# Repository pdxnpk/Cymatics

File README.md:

# Cymatics

Integrated PCBs for AudioLux and Vibrosonics

# Development

Install KiCad (version 8.0 or higher): https://www.kicad.org/download/

Open KiCad project file (Cymatics/Cymatics.kicad_pro)

# Build a PCB

## Order PCB

Go to JLCPCB (https://jlcpcb.com/) or PCBWay (https://www.pcbway.com/) to order a PCB

Start an order for a 2-layer PCB (Standard)

Add zip file of Gerber and Drill files (Fabrication/Cymatics_Gerber_Drill_03-21-25.zip)

Default specifications and options are OK

## Parts and Assembly

You may choose to have the PCB manufacturer assemble the boards for you, or you may order the parts separately and assemble the board on your own.

### Order PCB assembly

Provide the BOM and CPL (component placement list, or Centroid) for the manufacturer when requesting PCB assembly.

- Fabrication/Fabrication-BOM.xlsx: BOM adhering to PCBWay format (may need to revise for other manufacturers)

- Fabrication/Fabrication-CPL.csv: CPL or Centroid

### Order components separately

Open shopping list (Shopping-List.csv) to find links to order parts

Go to DigiKey (https://www.digikey.com/) and order listed part quanities

# Program the Microcontroller

To program the ESP32 with AudioLux and/or VibroSonics software, refer to their respective GitHub repositories.

- AudioLux software: https://github.com/OPEnSLab-OSU/Nanolux

- VibroSonics software: https://github.com/udellc/Vibrosonics

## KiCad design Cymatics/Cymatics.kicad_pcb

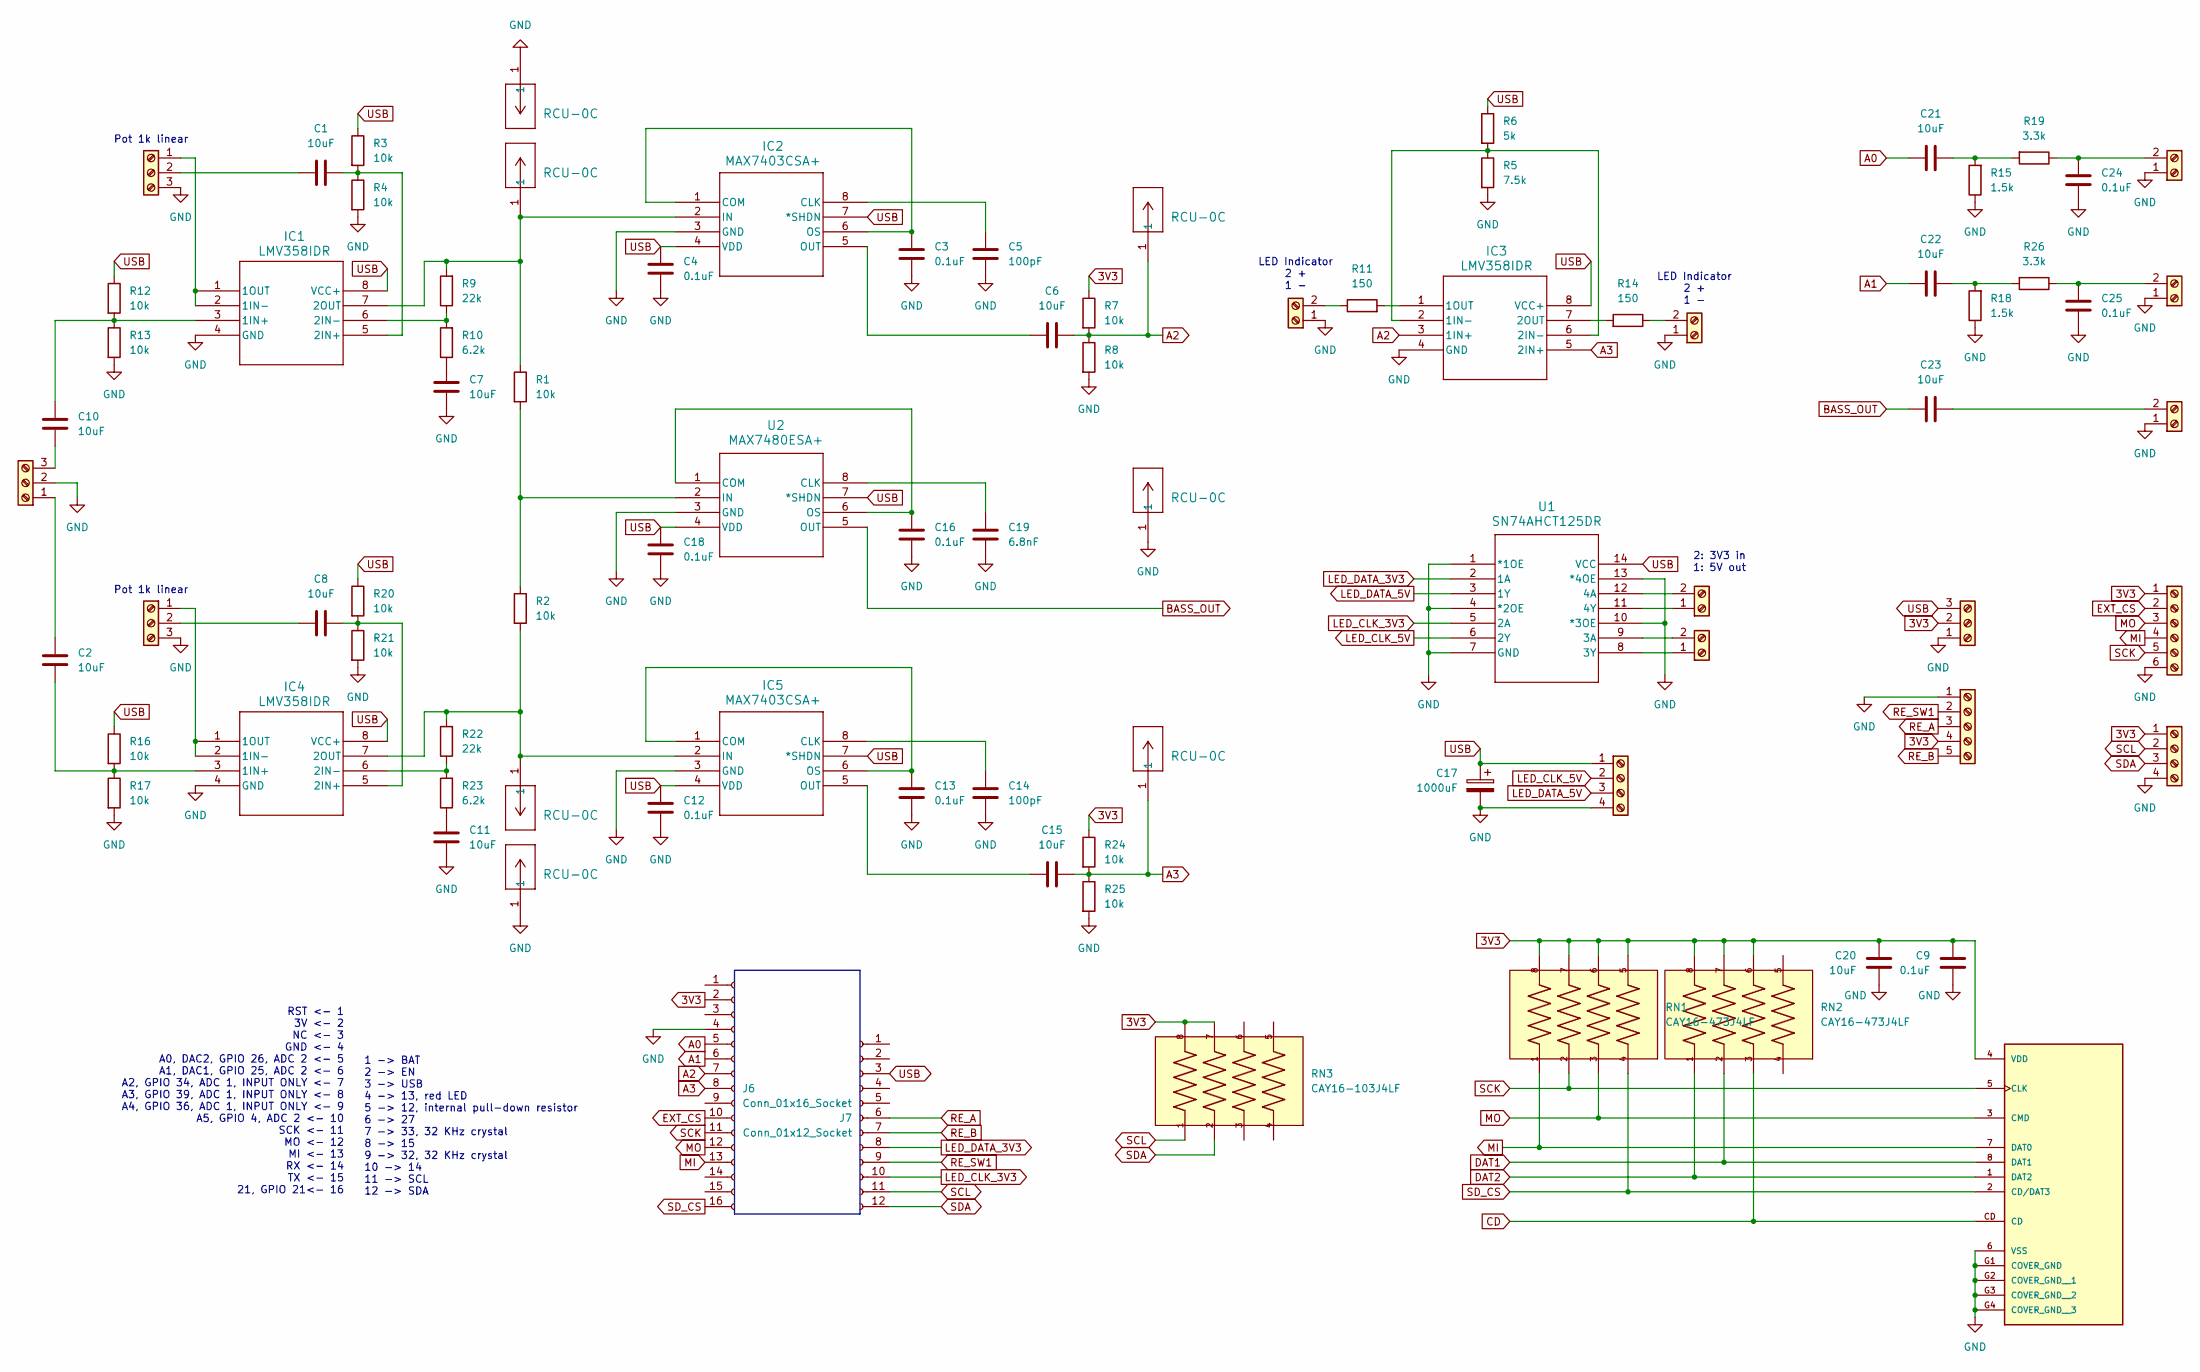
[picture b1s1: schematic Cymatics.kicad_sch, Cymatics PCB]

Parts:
C1, C2, C6, C7, C8, C10, C11, C15, C20, C21, C22, C23: 10uF; C_0805_2012Metric
C3, C4, C9, C12, C13, C16, C18, C24, C25: 0.1uF; C_0805_2012Metric
C5, C14: 100pF; C_0805_2012Metric
C17: 1000uF; CP_Radial_D8.0mm_P5.00mm
C19: 6.8nF; C_0805_2012Metric
IC1, IC3, IC4: LMV358IDR; D8
IC2, IC5: MAX7403CSA+; 21-0041B_8_MXM
J1, J3, J4, J16: Screw_Terminal_01x03; TerminalBlock_TE_282834-3_1x03_P2.54mm_Horizontal
J2, J5, J9, J12, J13, J15, J17: Screw_Terminal_01x02; TerminalBlock_TE_282834-2_1x02_P2.54mm_Horizontal
J6: Conn_01x16_Socket; PinSocket_1x16_P2.54mm_Vertical
J7: Conn_01x12_Socket; PinSocket_1x12_P2.54mm_Vertical
J8, J10: Screw_Terminal_01x04; TerminalBlock_TE_282834-4_1x04_P2.54mm_Horizontal
J11: Screw_Terminal_01x05; TerminalBlock_TE_282834-5_1x05_P2.54mm_Horizontal
J14, J19, J20, J21, J22, J23, J24: RCU-0C; CONN1_RCU-0C_TEC
J18: Screw_Terminal_01x06; TerminalBlock_TE_282834-6_1x06_P2.54mm_Horizontal
R1, R2, R3, R4, R7, R8, R12, R13, R16, R17, R20, R21, R24, R25: 10k; R_1206_3216Metric
R5: 7.5k; R_1206_3216Metric
R6: 5k; R_1206_3216Metric
R9, R22: 22k; R_1206_3216Metric
R10, R23: 6.2k; R_1206_3216Metric
R11, R14: 150; R_1206_3216Metric
R15, R18: 1.5k; R_1206_3216Metric
R19, R26: 3.3k; R_1206_3216Metric
RN1, RN2: CAY16-473J4LF; RESCAF80P320X160X60-8N
RN3: CAY16-103J4LF; RESCAF80P320X160X60-8N
SD1: MSD-4-A; CUI_MSD-4-A; PARTREV 1.0
U1: SN74AHCT125DR; D14
U2: MAX7480ESA+; 21-0041B_8_MXM

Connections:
3V3: C9.2, C20.1, J1.2, J6.2, J8.1, J11.4, J18.1, R7.1, R24.1, RN1.5, RN1.6, RN1.7, RN1.8, RN2.6, RN2.7, RN2.8, RN3.7, RN3.8, SD1.4 (VDD)
A0: C21.2, J6.5
A1: C22.2, J6.6
A2: C6.1, IC3.3 (1IN+), J6.7, J22.1, R7.2, R8.1
A3: C15.1, IC3.5 (2IN+), J6.8, J23.1, R24.2, R25.1
BASS_OUT: C23.2, U2.5 (OUT)
CD: RN2.3, SD1.CD
DAT1: RN2.2, SD1.8 (DAT1)
DAT2: RN2.1, SD1.1 (DAT2)
EXT_CS: J6.10, J18.2
GND: C3.1, C4.1, C5.1, C7.1, C9.1, C11.1, C12.1, C13.1, C14.1, C16.1, C17.2, C18.1, C19.1, C20.2, C24.1, C25.1, IC1.4 (GND), IC2.3 (GND), IC3.4 (GND), IC4.4 (GND), IC5.3 (GND), J1.1, J3.2, J4.3, J5.1, J6.4, J8.4, J10.4, J11.1, J12.1, J13.1, J15.1, J16.3, J17.1, J18.6, J19.1, J21.1, J24.1, R4.2, R5.2, R8.2, R13.2, R15.1, R17.2, R18.1, R21.2, R25.2, SD1.6 (VSS), SD1.G1 (COVER_GND), SD1.G2 (COVER_GND__1), SD1.G3 (COVER_GND__2), SD1.G4 (COVER_GND__3), U1.1 (*1OE), U1.4 (*2OE), U1.7 (GND), U1.10 (*3OE), U1.13 (*4OE), U2.3 (GND)
LED_CLK_3V3: J7.10, U1.5 (2A)
LED_CLK_5V: J10.2, U1.6 (2Y)
LED_DATA_3V3: J7.8, U1.2 (1A)
LED_DATA_5V: J10.3, U1.3 (1Y)
MI: J6.13, J18.4, RN1.1, SD1.7 (DAT0)
MO: J6.12, J18.3, RN1.3, SD1.3 (CMD)
unnamed: C7.2, R10.1
unnamed: C11.2, R23.1
unnamed: C21.1, R15.2, R19.2
unnamed: C22.1, R18.2, R26.2
unnamed: C10.1, IC1.3 (1IN+), R12.2, R13.1
unnamed: IC1.1 (1OUT), IC1.2 (1IN-), J4.1
unnamed: C1.1, IC1.5 (2IN+), R3.2, R4.1
unnamed: IC1.6 (2IN-), R9.1, R10.2
unnamed: IC1.7 (2OUT), IC2.2 (IN), J14.1, R1.1, R9.2
unnamed: C5.2, IC2.8 (CLK)
unnamed: C3.2, IC2.1 (COM), IC2.6 (OS)
unnamed: C6.2, IC2.5 (OUT)
unnamed: IC3.2 (1IN-), IC3.6 (2IN-), R5.1, R6.2
unnamed: IC3.1 (1OUT), R11.2
unnamed: IC3.7 (2OUT), R14.2
unnamed: C2.2, IC4.3 (1IN+), R16.2, R17.1
unnamed: IC4.1 (1OUT), IC4.2 (1IN-), J16.1
unnamed: C8.1, IC4.5 (2IN+), R20.2, R21.1
unnamed: IC4.6 (2IN-), R22.1, R23.2
unnamed: IC4.7 (2OUT), IC5.2 (IN), J20.1, R2.2, R22.2
unnamed: C14.2, IC5.8 (CLK)
unnamed: C13.2, IC5.1 (COM), IC5.6 (OS)
unnamed: C15.2, IC5.5 (OUT)
unnamed: J2.1, U1.11 (4Y)
unnamed: J2.2, U1.12 (4A)
unnamed: C2.1, J3.1
unnamed: C10.2, J3.3
unnamed: C1.2, J4.2
unnamed: J5.2, R11.1
unnamed: J9.1, U1.8 (3Y)
unnamed: J9.2, U1.9 (3A)
unnamed: C24.2, J12.2, R19.1
unnamed: C25.2, J13.2, R26.1
unnamed: J15.2, R14.1
unnamed: C8.2, J16.2
unnamed: C23.1, J17.2
unnamed: C19.2, U2.8 (CLK)
unnamed: C16.2, U2.1 (COM), U2.6 (OS)
unnamed: R1.2, R2.1, U2.2 (IN)
RE_A: J7.6, J11.3
RE_B: J7.7, J11.5
RE_SW1: J7.9, J11.2
SCK: J6.11, J18.5, RN1.2, SD1.5 (CLK)
SCL: J7.11, J8.2, RN3.1
SDA: J7.12, J8.3, RN3.2
SD_CS: J6.16, RN1.4, SD1.2 (CD/DAT3)
USB: C4.2, C12.2, C17.1, C18.2, IC1.8 (VCC+), IC2.4 (VDD), IC2.7 (*SHDN), IC3.8 (VCC+), IC4.8 (VCC+), IC5.4 (VDD), IC5.7 (*SHDN), J1.3, J7.3, J10.1, R3.1, R6.1, R12.1, R16.1, R20.1, U1.14 (VCC), U2.4 (VDD), U2.7 (*SHDN)

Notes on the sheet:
LED Indicator 2 + 1 -
Pot 1k linear
RST <- 1 3V <- 2 NC <- 3 GND <- 4 A0, DAC2, GPIO 26, ADC 2 <- 5 A1, DAC1, GPIO 25, ADC 2 <- 6 A2, GPIO 34, ADC 1, INPUT ONLY <- 7 A3, GPIO 39, ADC 1, INPUT ONLY <- 8 A4, GPIO 36, ADC 1, INPUT ONLY <- 9 A5, GPIO 4, ADC 2 <- 10 SCK <- 11 MO <- 12 MI <- 13 RX <- 14 TX <- 15 21, GPIO 21<- 16
1 -> BAT 2 -> EN 3 -> USB 4 -> 13, red LED 5 -> 12, internal pull-down resistor 6 -> 27 7 -> 33, 32 KHz crystal 8 -> 15 9 -> 32, 32 KHz crystal 10 -> 14 11 -> SCL 12 -> SDA
2: 3V3 in 1: 5V out

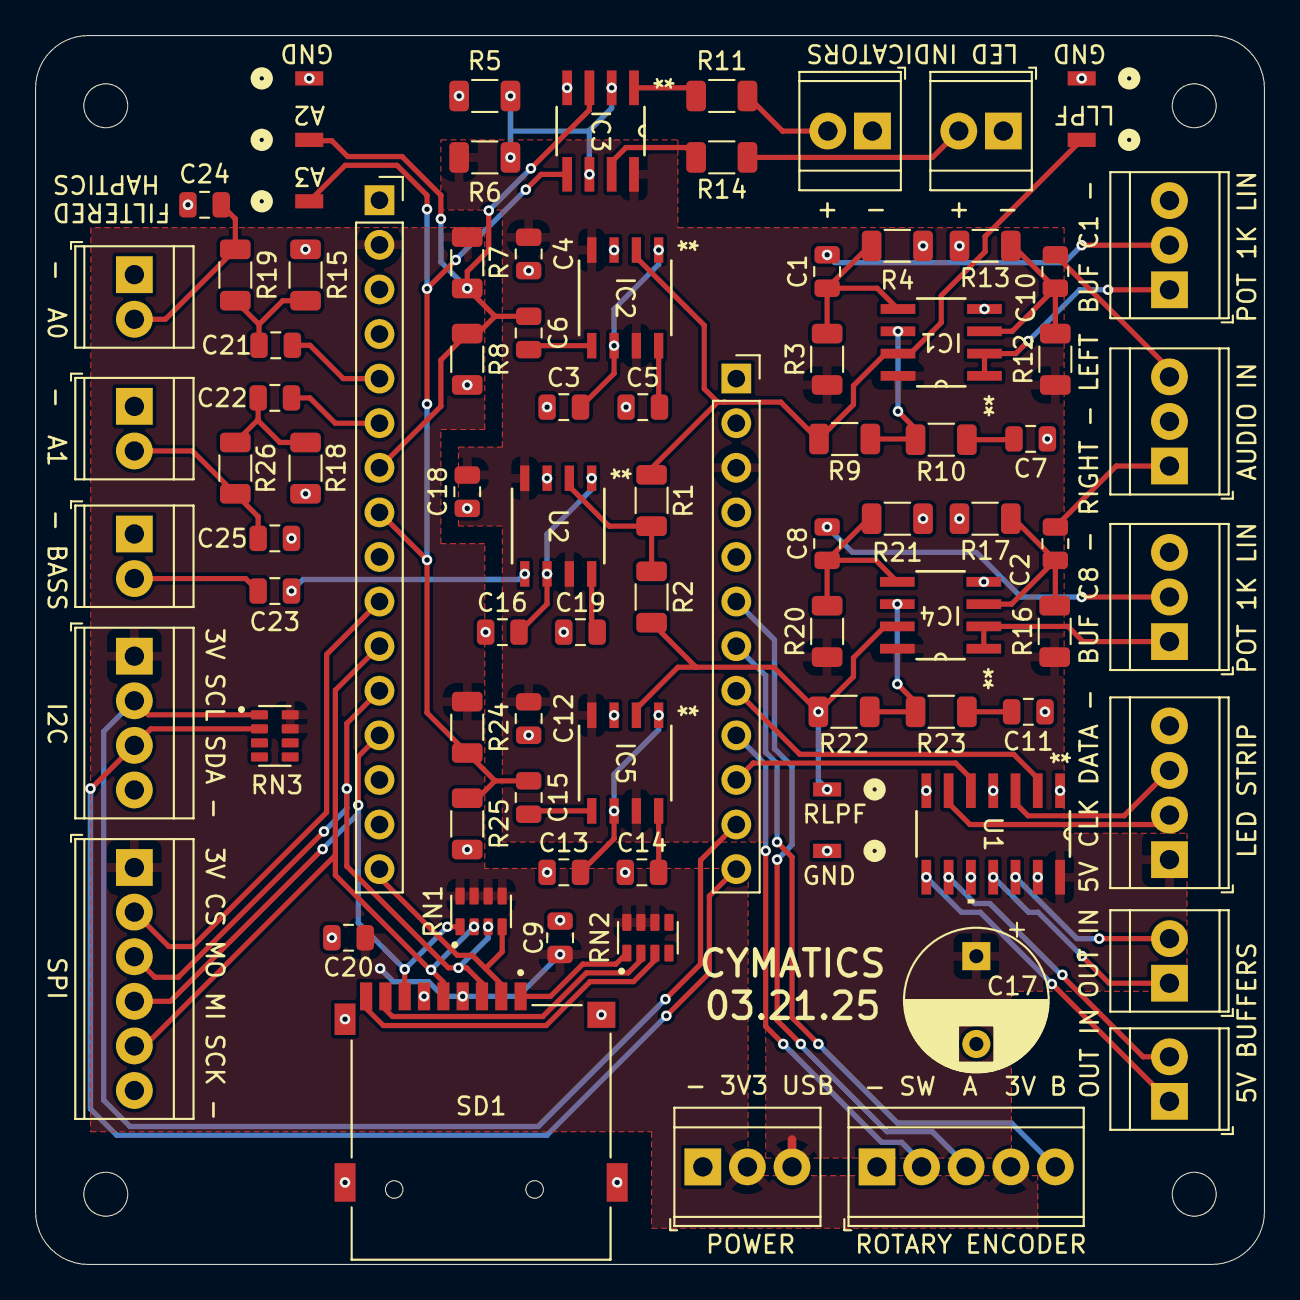
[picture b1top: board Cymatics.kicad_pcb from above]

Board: 2 copper layers, 70.0 x 70.0 mm, 86 parts (0 on the bottom side), 64 nets.

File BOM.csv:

Reference,Footprint,Value,Order Link (Datasheet),Qty
U1,D14,SN74AHCT125DR,https://www.digikey.com/en/products/detail/texas-instruments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,1
J18,TerminalBlock_TE-Connectivity:TerminalBlock_TE_282834-6_1x06_P2.54mm_Horizontal,Screw_Terminal_01x06,https://www.digikey.com/en/products/detail/te-connectivity-a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,1
J11,TerminalBlock_TE-Connectivity:TerminalBlock_TE_282834-5_1x05_P2.54mm_Horizontal,Screw_Terminal_01x05,https://www.digikey.com/en/products/detail/te-connectivity-a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,1
"J8,J10",TerminalBlock_TE-Connectivity:TerminalBlock_TE_282834-4_1x04_P2.54mm_Horizontal,Screw_Terminal_01x04,https://www.digikey.com/en/products/detail/te-connectivity-a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,2
"J1,J3,J4,J16",TerminalBlock_TE-Connectivity:TerminalBlock_TE_282834-3_1x03_P2.54mm_Horizontal,Screw_Terminal_01x03,https://www.digikey.com/en/products/detail/te-connectivity-a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,4
"J2,J5,J9,J12,J13,J15,J17",TerminalBlock_TE-Connectivity:TerminalBlock_TE_282834-2_1x02_P2.54mm_Horizontal,Screw_Terminal_01x02,https://www.digikey.com/en/products/detail/te-connectivity-a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,7
"J14,J19,J20,J21,J22,J23,J24",CONN1_RCU-0C_TEC,RCU-0C,https://www.digikey.com/en/products/detail/te-connectivity-a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,7
SD1,MSD-4-A:CUI_MSD-4-A,MSD-4-A,https://www.digikey.com/en/products/detail/same-sky-formerly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,1
U2,21-0041B_8_MXM,MAX7480ESA+,https://www.digikey.com/en/products/detail/analog-devices-in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,1
"IC2,IC5",21-0041B_8_MXM,MAX7403CSA+,https://www.digikey.com/en/products/detail/analog-devices-in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,2
"IC1,IC3,IC4",D8,LMV358IDR,https://www.digikey.com/en/products/detail/texas-instruments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,3
J6,Connector_PinSocket_2.54mm:PinSocket_1x16_P2.54mm_Vertical,Conn_01x16_Socket,https://www.digikey.com/en/products/detail/sullins-connector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,1
J7,Connector_PinSocket_2.54mm:PinSocket_1x12_P2.54mm_Vertical,Conn_01x12_Socket,https://www.digikey.com/en/products/detail/sullins-connector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,1
"RN1,RN2",CAY16-473:RESCAF80P320X160X60-8N,CAY16-473J4LF,https://www.digikey.com/en/products/detail/bourns-inc/CAY16-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,2
RN3,CAY16-103:RESCAF80P320X160X60-8N,CAY16-103J4LF,https://www.digikey.com/en/products/detail/bourns-inc/CAY16-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,1
"R9,R22",Resistor_SMD:R_1206_3216Metric,22k,https://www.digikey.com/en/products/detail/yageo/RC1206FR-07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,2
"R1,R2,R3,R4,R7,R8,R12,R13,R16,R17,R20,R21,R24,R25",Resistor_SMD:R_1206_3216Metric,10k,https://www.digikey.com/en/products/detail/yageo/RC1206FR-07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,14
R5,Resistor_SMD:R_1206_3216Metric,7.5k,https://www.digikey.com/en/products/detail/yageo/RC1206FR-07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,1
"R10,R23",Resistor_SMD:R_1206_3216Metric,6.2k,https://www.digikey.com/en/products/detail/yageo/RC1206FR-07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,2
R6,Resistor_SMD:R_1206_3216Metric,5k,https://www.digikey.com/en/products/detail/yageo/RT1206BRD07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,1
"R19,R26",Resistor_SMD:R_1206_3216Metric,3.3k,https://www.digikey.com/en/products/detail/yageo/RC1206FR-07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,2
"R15,R18",Resistor_SMD:R_1206_3216Metric,1.5k,https://www.digikey.com/en/products/detail/yageo/RC1206FR-07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,2
"R11,R14",Resistor_SMD:R_1206_3216Metric,150,https://www.digikey.com/en/products/detail/yageo/RC1206JR-07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,2
C17,Capacitor_THT:CP_Radial_D8.0mm_P5.00mm,1000uF,https://www.digikey.com/en/products/detail/rubycon/10ZLH1000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,1
"C1,C2,C6,C7,C8,C10,C11,C15,C20,C21,C22,C23",Capacitor_SMD:C_0805_2012Metric,10uF,https://www.digikey.com/en/products/detail/yageo/CC0805ZKY5V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,12
"C3,C4,C9,C12,C13,C16,C18,C24,C25",Capacitor_SMD:C_0805_2012Metric,0.1uF,https://www.digikey.com/en/products/detail/yageo/CC0805KRX7R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,9
C19,Capacitor_SMD:C_0805_2012Metric,6.8nF,https://www.digikey.com/en/products/detail/yageo/CC0805KRX7R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,1
"C5,C14",Capacitor_SMD:C_0805_2012Metric,100pF,https://www.digikey.com/en/products/detail/yageo/CC0805JRNPO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,2
,,,,
External Modules,Part Number,,Order Link (Datasheet),
Stereo Pot 1k linear,PDB182-K220K-102B,,https://www.digikey.com/en/products/detail/bourns-inc/PDB182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,1
Rotary Encoder,PEC11R-4215F-S0024,,https://www.digikey.com/en/products/detail/bourns-inc/PEC11R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,1
Stereo Jack 3.5mm,35PRM3,,https://www.digikey.com/en/products/detail/switchcraft-inc/3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,1
Buck Converter,DFR1015,,https://www.digikey.com/en/products/detail/dfrobot/DFR1015/18069278,1
Red LED,C503B-RAN-CA0B0AA1,,https://www.digikey.com/en/products/detail/cree-led/C503B-RA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,2

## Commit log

2025-01-29 Copy AudioLux and Cymatics into repo
2025-01-29 rel paths for AudioLux footprints/symbols library
2025-01-29 resolved all DRC errors
2025-01-31 added testpoints
2025-01-31 testpoints update and terminal block labels
2025-02-01 swizzled rotary encoder block
2025-02-02 new testpoint RCU-0C
2025-02-02 changes and Gerber Drill generate for order
2025-02-02 added cymatics label and ordered PCB and parts
2025-02-22 changed positioning of blocks for diagrams
2025-02-23 pull up resistors for SPI and I2C
2025-02-26 use 10k pullup for I2C and DAT1/2
2025-02-27 Order for March PCB
2025-03-12 All changes up through Week 9, including making the step file
2025-03-12 added passive DAC filters to schem and layout
2025-05-04 misc updates
2025-05-18 bom and gerber zip
2025-05-24 fab folder
2025-05-26 xlsx BOM for PCBWay
2025-05-27 add shopping list
